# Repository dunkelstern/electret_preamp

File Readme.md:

# Electret Microphone Preamp

This design is purely based on [Texas Instruments Single-Supply, Electret Microphone Pre-Amplifier Reference Design by John Caldwell](http://www.ti.com/lit/ug/tidu765/tidu765.pdf?ts=1590780945605)

The Jupyter notebook is basically a interactive Version of that reference design PDF. I claim no copyright on this.

## What you will find here

### Jupyter Notebook

The included Jupyter Notebook is an interactive version of the reference design PDF from Texas instruments. You can
play with all values and let the program re-calculate all relevant values to be used in your own design.

There are some areas that will be most important:

- Operating Voltage of the Preamp

- Parameters of the Microphone capsule in use

- Acceptable high-frequency attenuation

- Acceptable low-frequency cutoff in output highpass filter

- The List of passive component values

- The Op-Amp parameters to look out for

### LT Spice simulation

I have simulated the circuit in LTSpice with some different Op-Amps I had in stock.
I deviated from the `270k` resistor in the Op-Amp feedback loop and opted for a `180k` value. This
means the amplification of the Op-Amp will not reach `0dB` (max. seems to be around `-1.8dB`) but the circuit seems
to run more stable at that amplification.

Here are some bode-plots of the frequency response for some tested Op-Amps:

#### OP07

The OP07 is the worst possible of the bunch. The bad response is a product of the sub-optimal slew rate of .
Additionally this Op-Amp will add noise to the signal as it's input voltage noise is around . Ideally
it should be below  as we can see in the calulations.

#### TL072

The TL072 is a bit better than the OP07. The slew rate of  is at least enough.
This Op-Amp will add a lot of noise to the signal as it's input voltage noise is around . Ideally
it should be below  as we can see in the calulations.

#### NE5532

The NE5532 is really good at this. All parameters are within the parameter range we calculated.

#### LM318

You can see why the LM318 is used for these applications a lot, as it is a dedicated Audio-Op-Amp the response from
this thing is the best of the bunch.

**Attention**: The `LM318` needed `5.3V` operating voltage to actually do anything in the simulation, I have not
verified if this is an artifact of the simulation or an actual problem!

### KiCAD design

The KiCAD design is based on surface mount components to save as much space as possible. You could use tantalum
capacitors instead of the electrolyte I used here, but they are expensive and I don't have them in stock.

The board design is optimized for space and to be single sided as it is easier to prototype this way.
I will probably add a better two sided design in the future which will be optimized for noise performance and
will probably get even smaller (but I have to order the PCBs then)

This is what the board looks like rendered, I will add a photo of the finished product when I have built one.

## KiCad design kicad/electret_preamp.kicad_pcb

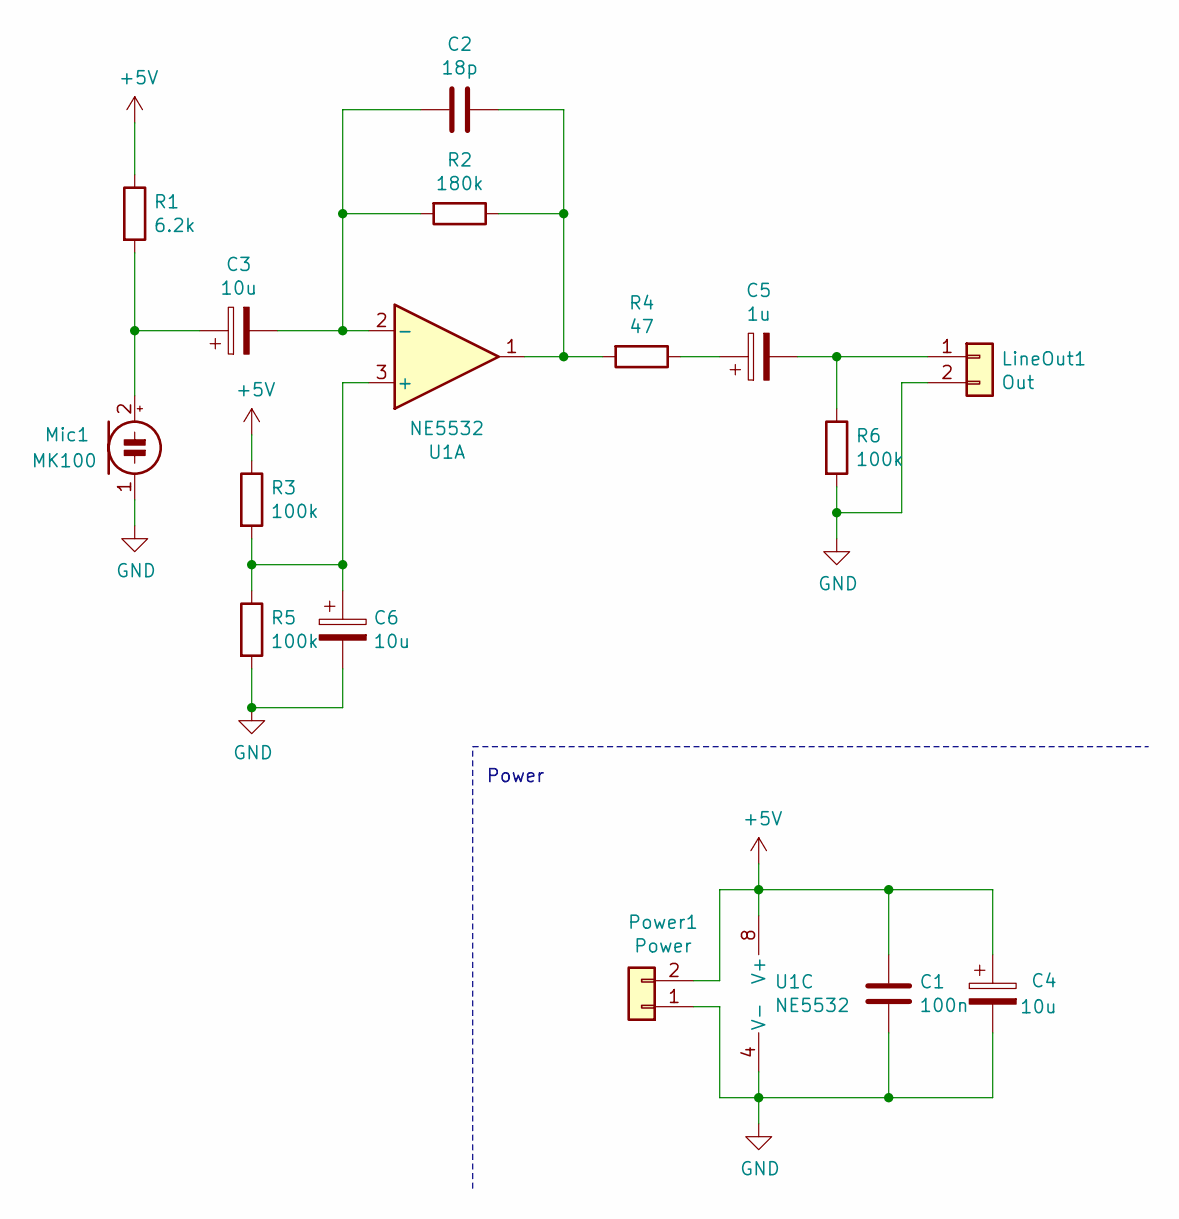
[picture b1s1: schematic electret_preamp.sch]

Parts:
C1: 100n; C_1210_3225Metric_Pad1.42x2.65mm_HandSolder
C2: 18p; C_0805_2012Metric_Pad1.15x1.40mm_HandSolder
C3, C6: 10u; CP_Elec_4x5.8
C4: 10u; CP_Elec_6.3x9.9
C5: 1u; CP_Elec_4x5.8
LineOut1: Out; PinHeader_1x02_P2.54mm_Horizontal
Mic1: MK100; PinHeader_1x02_P2.54mm_Horizontal
Power1: Power; PinHeader_1x02_P2.54mm_Horizontal
R1: 6.2k; R_1210_3225Metric_Pad1.42x2.65mm_HandSolder
R2: 180k; R_1210_3225Metric_Pad1.42x2.65mm_HandSolder
R3, R5, R6: 100k; R_1210_3225Metric_Pad1.42x2.65mm_HandSolder
R4: 47; R_1210_3225Metric_Pad1.42x2.65mm_HandSolder
U1: NE5532; SOIC-8_3.9x4.9mm_P1.27mm

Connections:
+5V: C1.2, C4.1, Power1.2, R1.1, R3.1, U1.8 (V+)
GND: C1.1, C4.2, C6.2, LineOut1.2, Mic1.1 (-), Power1.1, R5.2, R6.2, U1.4 (V-)
unnamed: C2.1, R2.1, R4.2, U1.1
unnamed: C2.2, C3.2, R2.2, U1.2 (-)
unnamed: C3.1, Mic1.2 (+), R1.2
unnamed: C5.1, R4.1
unnamed: C5.2, LineOut1.1, R6.1
unnamed: C6.1, R3.2, R5.1, U1.3 (+)

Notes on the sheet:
Power

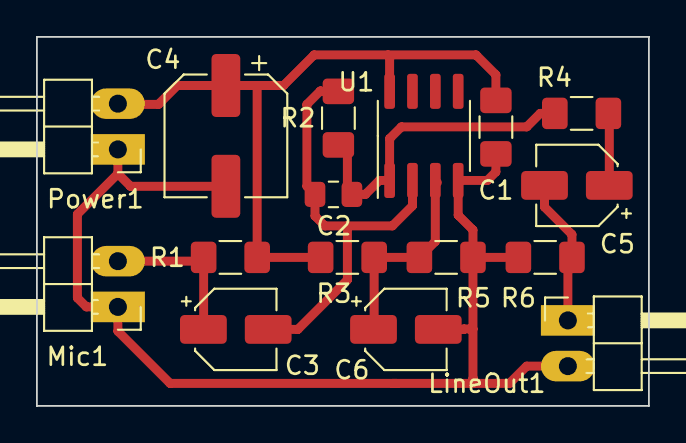
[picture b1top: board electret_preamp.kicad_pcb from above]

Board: 2 copper layers, 34.0 x 20.5 mm, 16 parts (0 on the bottom side), 8 nets.

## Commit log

2020-05-31 Jupyter Notebook
2020-05-31 Board layout (KiCAD)
2020-05-31 Images for Readme.md
2020-05-31 Fix errors in KiCAD files
2020-05-31 OP-AMP in wrong direction in schematic
2020-05-31 Add LTSpice simulation for multiple different OpAmps
2020-05-31 Ignore temporary files
2020-05-31 Add readme
2020-05-31 Readme layout
2020-05-31 Sometimes I hate markdown
2020-05-31 Math
2020-05-31 Typo
2020-05-31 Bugfix: URL for math not valid
2020-05-31 Polarized cap in wrong direction
2020-06-02 Some layout fixes
